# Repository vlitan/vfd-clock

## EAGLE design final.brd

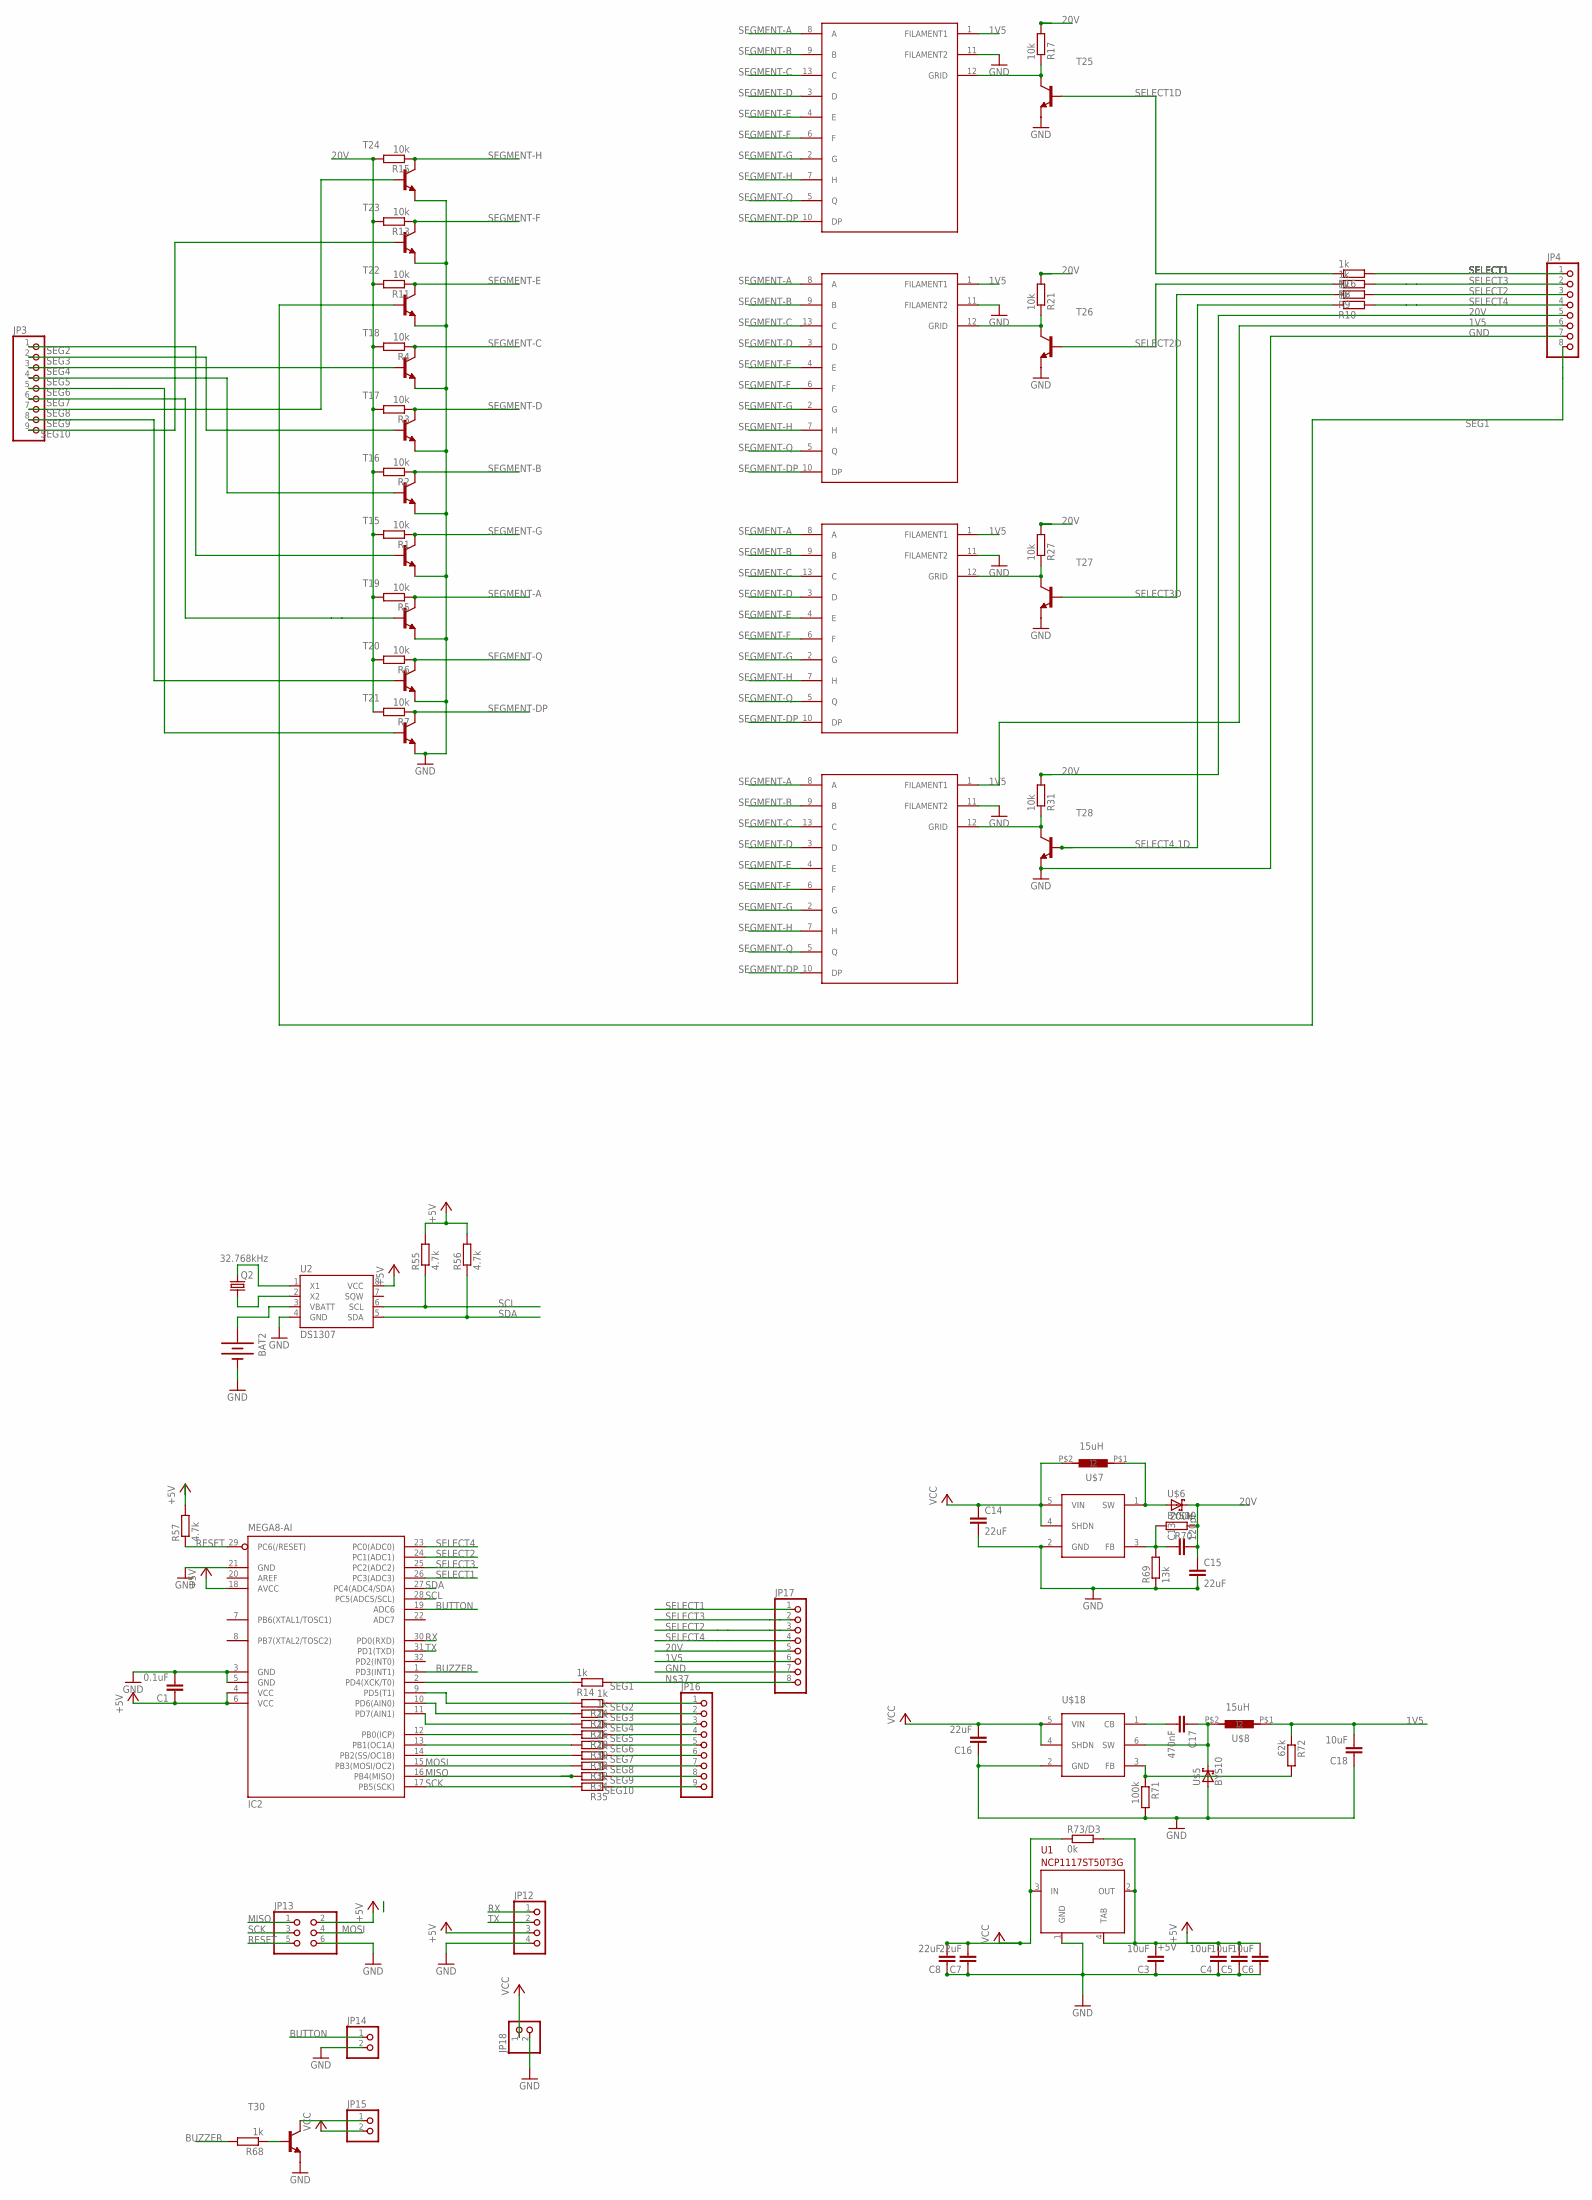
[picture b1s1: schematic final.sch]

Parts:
BAT2: BATTERY12PTH; BATTCON_12MM_PTH
C1: 0.1uF; C1206
C3, C4, C5, C6, C18: 10uF; C1206
C7, C8, C14, C15, C16: 22uF; C1206
C13: 120pF; C1206
C17: 470nF; C1206
IC2: MEGA8-AI; TQFP32-08
JP3, JP16: PINHD-1X9; 1X09
JP4, JP17: PINHD-1X8; 1X08
JP12: PINHD-1X04_2.54-S; 1X04-S
JP13: PINHD-2X03_2.54; 2X03
JP14, JP15: PINHD-1X02_2.54; 1X02
JP18: PINHD-1X2; 1X02
Q2: 32.768kHz; CRYSTAL-32KHZ-SMD
R1, R2, R3, R4, R5, R6, R7, R11, R13, R15, R17, R21, R27, R31: 10k; R1206
R8, R9, R10, R14, R16, R24, R25, R26, R28, R30, R32, R33, R34, R35, R68: 1k; R1206
R55, R56, R57: 4.7k; R1206
R69: 13k; R1206
R70: 200k; R1206
R71: 100k; R1206
R72: 62k; R1206
R73/D3: 0k; R1206
T15, T16, T17, T18, T19, T20, T21, T22, T23, T24, T25, T26, T27, T28, T30: BC817-25-NPN-SOT23-BEC; SOT23-BEC
U1: NCP1117ST50T3G; SOT223
U2: DS1307; SO08-TIGHT
U$1, U$2, U$3, U$4: VFD; ROUND-THT
U$5, U$6: BYS10; DO-214AC
U$7, U$8: 15uH; DJNR5020
U$15: LM27313DEV; SOT-23
U$18: LMR14206DEV; SOT-23

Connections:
1V5: C18.2, JP4.6, JP17.6, R72.1, U$1.1 (FILAMENT1), U$2.1 (FILAMENT1), U$3.1 (FILAMENT1), U$4.1 (FILAMENT1), U$8.P$1 (1)
20V: C13.2, C15.1, JP4.5, JP17.5, R1.2, R2.2, R3.2, R4.2, R5.2, R6.2, R7.2, R11.2, R13.2, R15.2, R17.2, R21.2, R27.2, R31.2, R70.1, U$6.2 (C)
+5V: C1.1, C3.2, C4.2, C5.2, C6.2, IC2.4 (VCC), IC2.6 (VCC), IC2.18 (AVCC), JP12.3, JP13.2, R55.2, R56.2, R57.2, R73/D3.2, U1.2 (OUT), U1.4 (TAB), U2.8 (VCC)
BUTTON: IC2.19 (ADC6), JP14.1
BUZZER: IC2.1 (PD3(INT1)), R68.2
GND: BAT2.GND (-), C1.2, C3.1, C4.1, C5.1, C6.1, C7.1, C8.1, C14.2, C15.2, C16.1, C18.1, IC2.3 (GND), IC2.5 (GND), IC2.21 (GND), JP4.7, JP12.4, JP13.6, JP14.2, JP17.7, JP18.2, R69.1, R71.2, T15.E, T16.E, T17.E, T18.E, T19.E, T20.E, T21.E, T22.E, T23.E, T24.E, T25.E, T26.E, T27.E, T28.E, T30.E, U1.1 (GND), U2.4 (GND), U$1.11 (FILAMENT2), U$2.11 (FILAMENT2), U$3.11 (FILAMENT2), U$4.11 (FILAMENT2), U$5.1 (A), U$15.2 (GND), U$18.2 (GND)
MISO: IC2.16 (PB4(MISO)), JP13.1, R34.2
MOSI: IC2.15 (PB3(MOSI/OC2)), JP13.4, R32.2
unnamed: R17.1, T25.C, U$1.12 (GRID)
unnamed: IC2.14 (PB2(SS/OC1B)), R33.2
unnamed: IC2.13 (PB1(OC1A)), R30.2
unnamed: R21.1, T26.C, U$2.12 (GRID)
unnamed: IC2.12 (PB0(ICP)), R28.2
unnamed: IC2.11 (PD7(AIN1)), R26.2
unnamed: R27.1, T27.C, U$3.12 (GRID)
unnamed: R31.1, T28.C, U$4.12 (GRID)
unnamed: IC2.10 (PD6(AIN0)), R25.2
unnamed: IC2.9 (PD5(T1)), R24.2
unnamed: IC2.2 (PD4(XCK/T0)), R14.1
unnamed: Q2.X2 (2), U2.1 (X1)
unnamed: Q2.X1 (1), U2.2 (X2)
unnamed: BAT2.VCC@1 (+), U2.3 (VBATT)
unnamed: JP15.1, T30.C
unnamed: R68.1, T30.B
unnamed: U$6.1 (A), U$7.P$1 (1), U$15.1 (SW)
unnamed: C13.1, R69.2, R70.2, U$15.3 (FB)
unnamed: R71.1, R72.2, U$18.3 (FB)
unnamed: C17.1, U$5.2 (C), U$8.P$2 (2), U$18.6 (SW)
unnamed: C17.2, U$18.1 (CB)
RESET: IC2.29 (PC6(/RESET)), JP13.5, R57.1
RX: IC2.30 (PD0(RXD)), JP12.1
SCK: IC2.17 (PB5(SCK)), JP13.3, R35.2
SCL: IC2.28 (PC5(ADC5/SCL)), R55.1, U2.6 (SCL)
SDA: IC2.27 (PC4(ADC4/SDA)), R56.1, U2.5 (SDA)
SEG1: JP4.8, JP17.8, R14.2, T22.B
SEG2: JP3.1, JP16.1, R24.1, T15.B
SEG3: JP3.2, JP16.2, R25.1, T17.B
SEG4: JP3.3, JP16.3, R26.1, T18.B
SEG5: JP3.4, JP16.4, R28.1, T16.B
SEG6: JP3.5, JP16.5, R30.1, T21.B
SEG7: JP3.6, JP16.6, R33.1, T19.B
SEG8: JP3.7, JP16.7, R32.1, T24.B
SEG9: JP3.8, JP16.8, R34.1, T20.B
SEG10: JP3.9, JP16.9, R35.1, T23.B
SEGMENT-A: R5.1, T19.C, U$1.8 (A), U$2.8 (A), U$3.8 (A), U$4.8 (A)
SEGMENT-B: R2.1, T16.C, U$1.9 (B), U$2.9 (B), U$3.9 (B), U$4.9 (B)
SEGMENT-C: R4.1, T18.C, U$1.13 (C), U$2.13 (C), U$3.13 (C), U$4.13 (C)
SEGMENT-D: R3.1, T17.C, U$1.3 (D), U$2.3 (D), U$3.3 (D), U$4.3 (D)
SEGMENT-DP: R7.1, T21.C, U$1.10 (DP), U$2.10 (DP), U$3.10 (DP), U$4.10 (DP)
SEGMENT-E: R11.1, T22.C, U$1.4 (E), U$2.4 (E), U$3.4 (E), U$4.4 (E)
SEGMENT-F: R13.1, T23.C, U$1.6 (F), U$2.6 (F), U$3.6 (F), U$4.6 (F)
SEGMENT-G: R1.1, T15.C, U$1.2 (G), U$2.2 (G), U$3.2 (G), U$4.2 (G)
SEGMENT-H: R15.1, T24.C, U$1.7 (H), U$2.7 (H), U$3.7 (H), U$4.7 (H)
SEGMENT-Q: R6.1, T20.C, U$1.5 (Q), U$2.5 (Q), U$3.5 (Q), U$4.5 (Q)
SELECT1: IC2.26 (PC3(ADC3)), JP4.1, JP17.1, R16.2
SELECT1D: R16.1, T25.B
SELECT2: IC2.24 (PC1(ADC1)), JP4.3, JP17.3, R9.2
SELECT2D: R8.1, T26.B
SELECT3: IC2.25 (PC2(ADC2)), JP4.2, JP17.2, R8.2
SELECT3D: R9.1, T27.B
SELECT4: IC2.23 (PC0(ADC0)), JP4.4, JP17.4, R10.2
SELECT4.1D: R10.1, T28.B
TX: IC2.31 (PD1(TXD)), JP12.2
VCC: C7.2, C8.2, C14.1, C16.2, JP15.2, JP18.1, R73/D3.1, U1.3 (IN), U$7.P$2 (2), U$15.4 (SHDN), U$15.5 (VIN), U$18.4 (SHDN), U$18.5 (VIN)

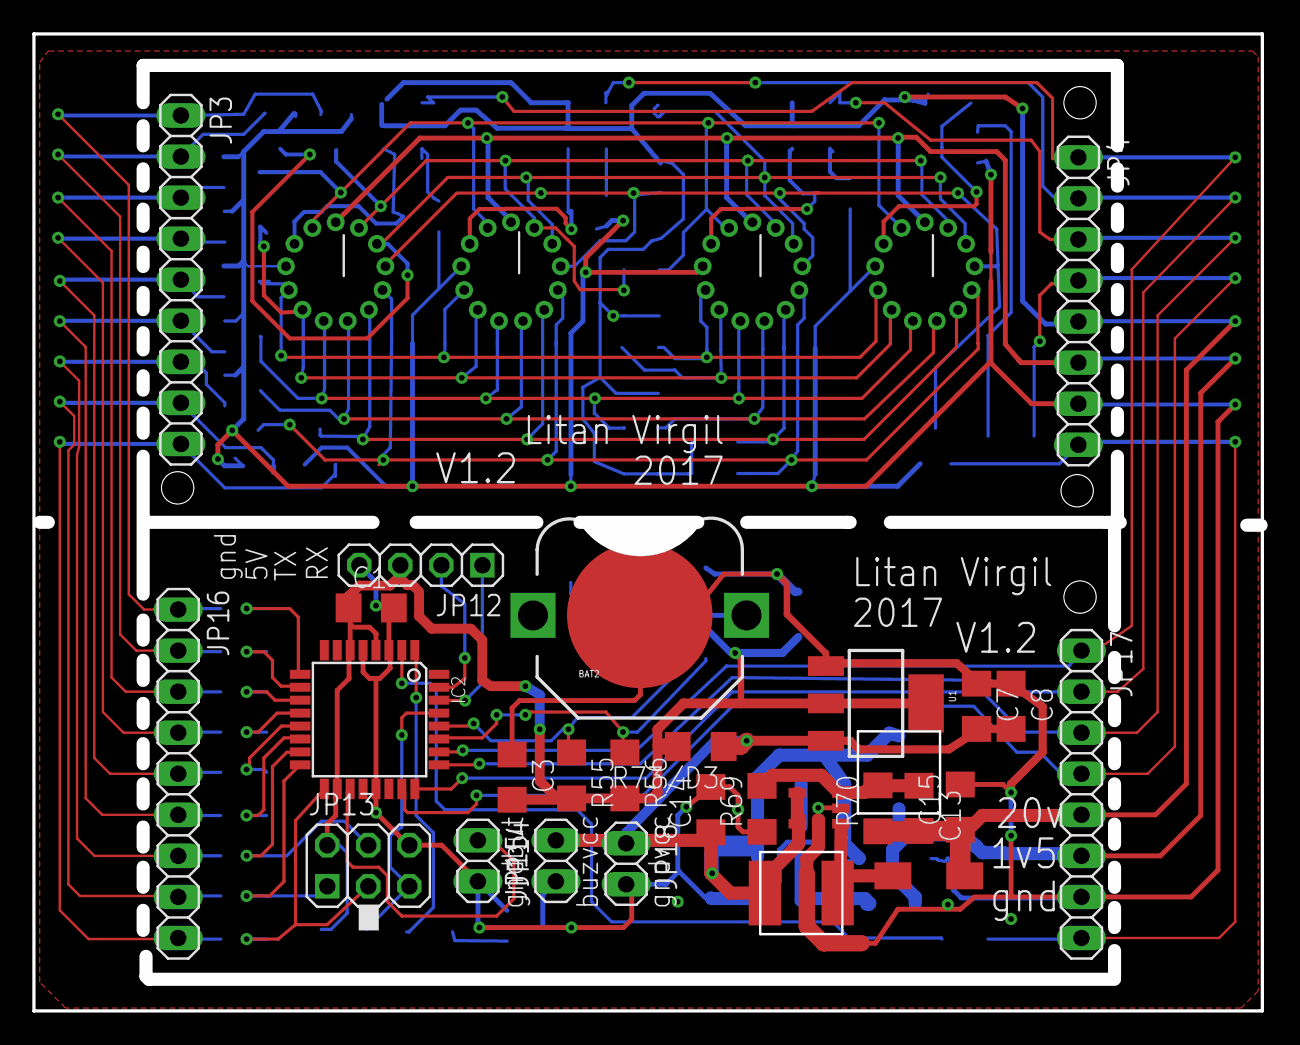
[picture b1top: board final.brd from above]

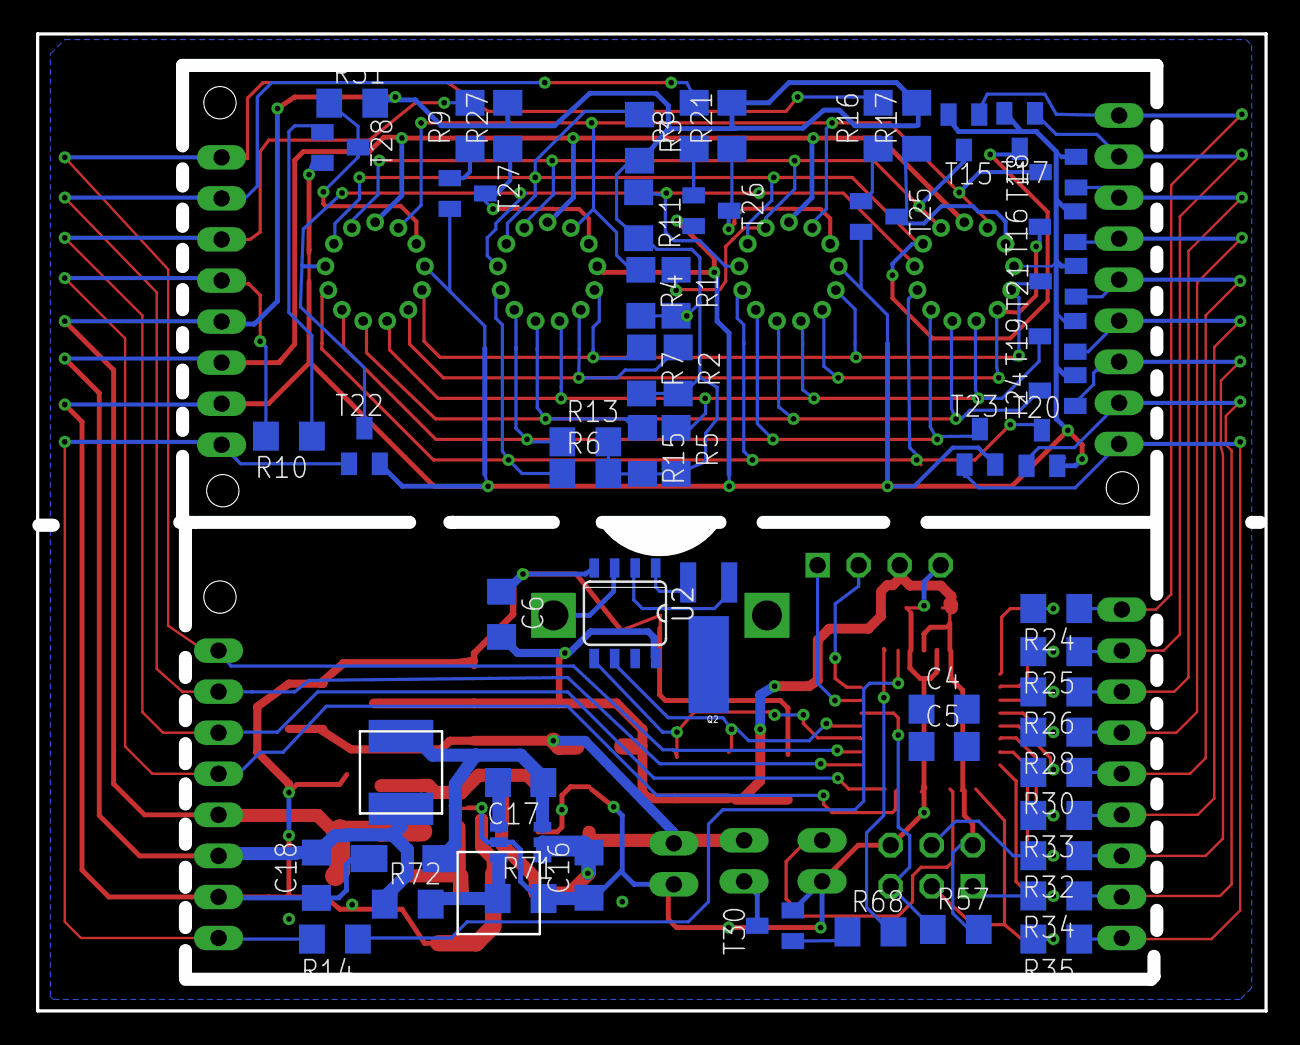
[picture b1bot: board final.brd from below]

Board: 2 copper layers, 76.0 x 60.4 mm, 89 parts (58 on the bottom side), 64 nets.

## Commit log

2017-08-26 final tweaks
2017-08-26 added holes and milling
2017-08-26 adjusted footprint of inductors and diodes in a really nasty and non-ok way
2017-08-26 adjusted distance between vfds and moved name from top to tPlace layer
2017-09-06 adjusted battery position and cleaned up the driver
2017-11-12 moved 1k resisitors on logic board, more compact. fixed inductor, diode and 7805 packages. TODO add ground plane, move holes, add milling
2017-11-13 srinkified logic board
2017-11-13 shrinkified driver board. not OK
2017-11-13 added todo
2017-11-14 driver board update, all components on bottom. still to large
2017-11-15 thicker power-lines, smaller driver
2017-11-15 fixed big issue on driver
2017-11-15 small details done
2017-11-23 thicker traces for switching supplies. milling almost done
2017-11-24 added pin naming
2017-11-29 modified feedback network for buck supply
2017-11-29 fixed mirrored vfd layout
2017-11-29 added groundplane, replaced 5v regulator, added extra capacitors and optional diode / 0kresistor
2017-11-29 added milling layer, ground plane

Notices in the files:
parts and their libraries:
SparkFun-Electromechanical: Licensing: CC v3.0 Share-Alike You are welcome to use this library for commercial purposes.
